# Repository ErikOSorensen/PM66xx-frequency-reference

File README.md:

# PM66xx-frequency-reference

The plan is to build a good 10MHz reference for a PM6674 frequency counter (and those that are related).
This will be a gift to a lucky owner of such a counter.

Inspiration (and physical measurements) are taken from [The sync channel](https://syncchannel.blogspot.com/2016/04/flukephilips-pm66xx-frequency-counter.html),
but I am not so sure about using the internal voltage reference of the oscillator module. I would rather use an external low tempco 
reference such as the [ADR434BRZ](https://www.analog.com/en/products/adr434.html), which means I also need to add
a voltage regulator for this chip.

Looking at the output of my spare CTS 970 oscillator, I think it would also be nice to provide 
a filter on the output, and I've added a 10.5 MHz low pass filter on the bottom of the board.

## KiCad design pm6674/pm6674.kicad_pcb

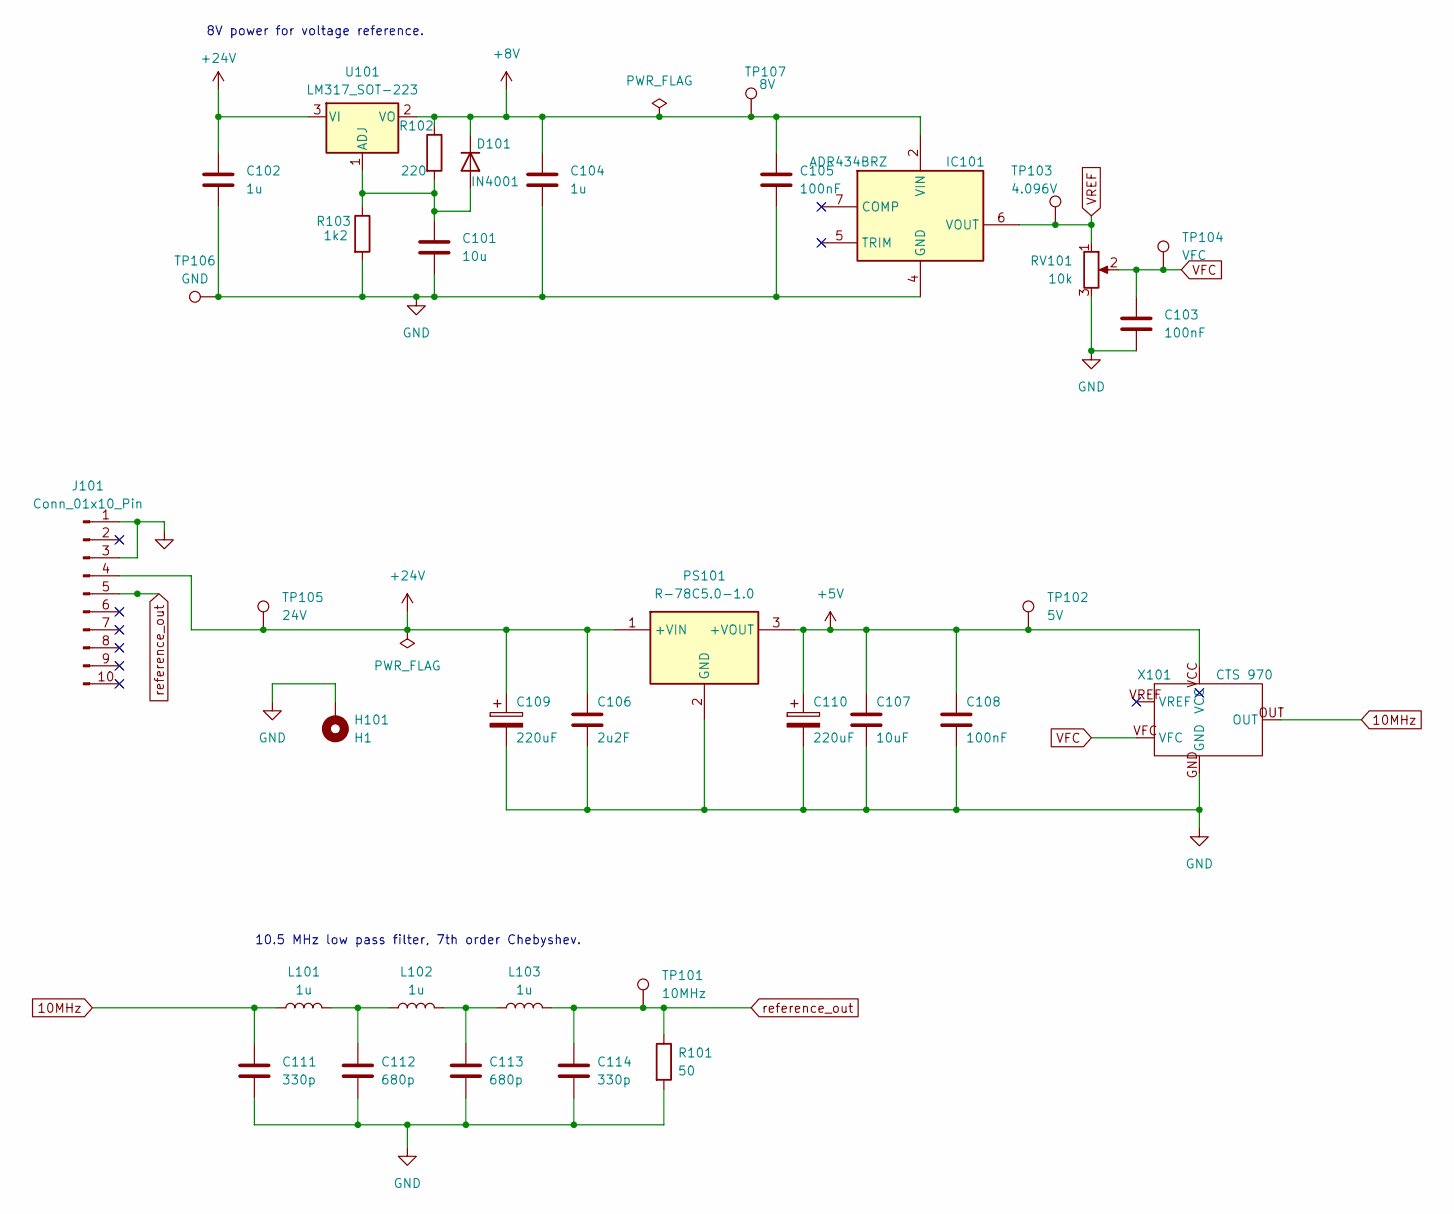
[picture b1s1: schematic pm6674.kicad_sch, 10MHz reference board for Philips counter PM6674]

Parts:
C101: 10u; C_0805_2012Metric
C102, C104: 1u; C_0805_2012Metric
C103, C105, C108: 100nF; C_0805_2012Metric
C106: 2u2F; C_0805_2012Metric
C107: 10uF; C_0805_2012Metric
C109, C110: 220uF; CP_Elec_8x10.5
C111, C114: 330p; C_0805_2012Metric
C112, C113: 680p; C_0805_2012Metric
D101: IN4001; D_SOD-123F
H101: H1; MountingHole_3.2mm_M3_DIN965_Pad_TopBottom
IC101: ADR434BRZ; SOIC127P600X175-8N; Mouser Part Number 584-ADR434BRZ
J101: Conn_01x10_Pin; Molex 22-14-2104
L101, L102, L103: 1u; L_0805_2012Metric
PS101: R-78C5.0-1.0; R78C1210; Mouser Part Number 919-R-78C5.0-1.0
R101: 50; R_0805_2012Metric
R102: 220; R_0805_2012Metric
R103: 1k2; R_0805_2012Metric
RV101: 10k; M64Y503KB40
TP101: 10MHz; PinHeader_1x01_P2.54mm_Vertical
TP102: 5V; PinHeader_1x01_P2.54mm_Vertical
TP103: 4.096V; PinHeader_1x01_P2.54mm_Vertical
TP104: VFC; PinHeader_1x01_P2.54mm_Vertical
TP105: 24V; PinHeader_1x01_P2.54mm_Vertical
TP106: GND; PinHeader_1x01_P2.54mm_Vertical
TP107: 8V; PinHeader_1x01_P2.54mm_Vertical
U101: LM317_SOT-223; SOT-223-3_TabPin2
X101: CTS 970; CTS1960017

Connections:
10MHz: C111.1, L101.1, X101.OUT
+5V: C107.1, C108.1, C110.1, PS101.3 (+VOUT), TP102.1, X101.VCC
+8V: C104.1, C105.1, D101.1 (K), IC101.2 (VIN), R102.1, TP107.1, U101.2 (VO)
+24V: C102.1, C106.1, C109.1, J101.4, PS101.1 (+VIN), TP105.1, U101.3 (VI)
GND: C101.2, C102.2, C103.2, C104.2, C105.2, C106.2, C107.2, C108.2, C109.2, C110.2, C111.2, C112.2, C113.2, C114.2, H101.1, IC101.4 (GND), J101.1, J101.3, PS101.2 (GND), R101.2, R103.2, RV101.3, TP106.1, X101.GND
unnamed: C112.1, L101.2, L102.1
unnamed: C113.1, L102.2, L103.1
unnamed: C101.1, D101.2 (A), R102.2, R103.1, U101.1 (ADJ)
VFC: C103.1, RV101.2, TP104.1, X101.VFC
VREF: IC101.6 (VOUT), RV101.1, TP103.1
reference_out: C114.1, J101.5, L103.2, R101.1, TP101.1

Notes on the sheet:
10.5 MHz low pass filter, 7th order Chebyshev.
8V power for voltage reference.

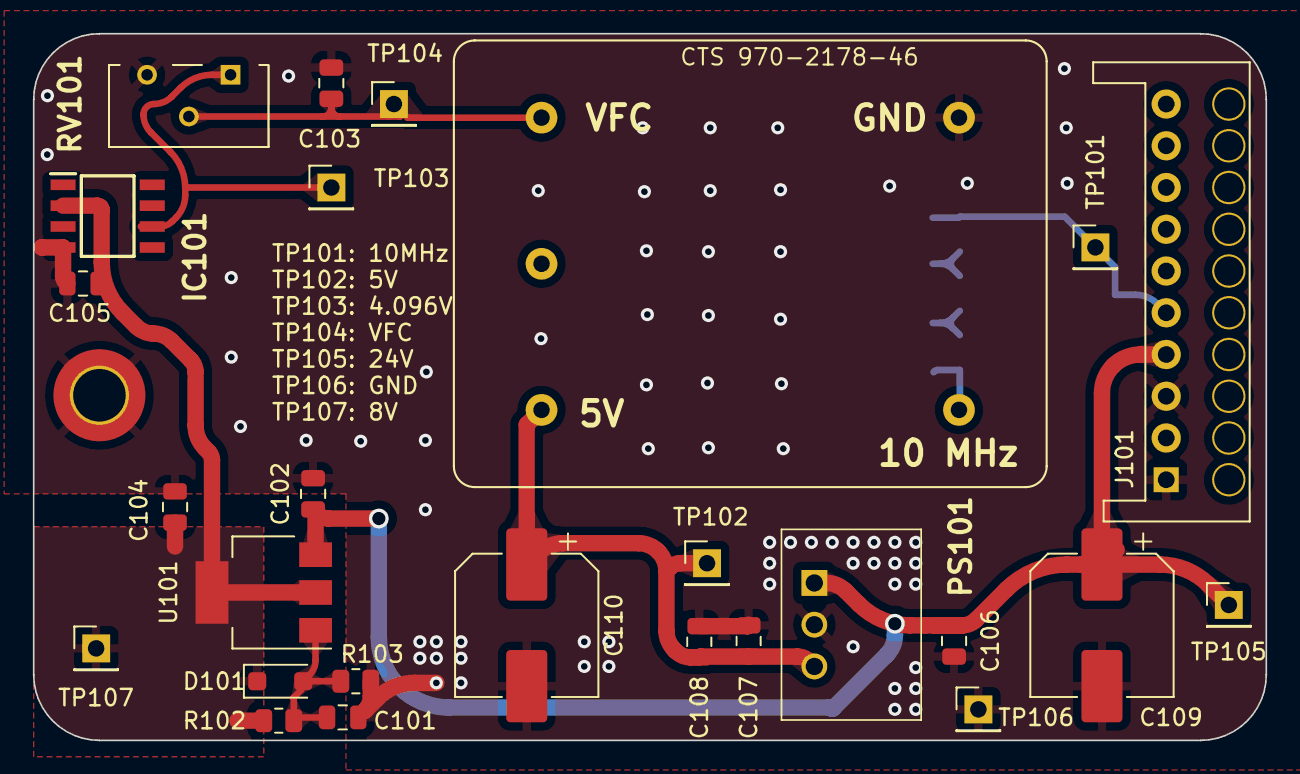
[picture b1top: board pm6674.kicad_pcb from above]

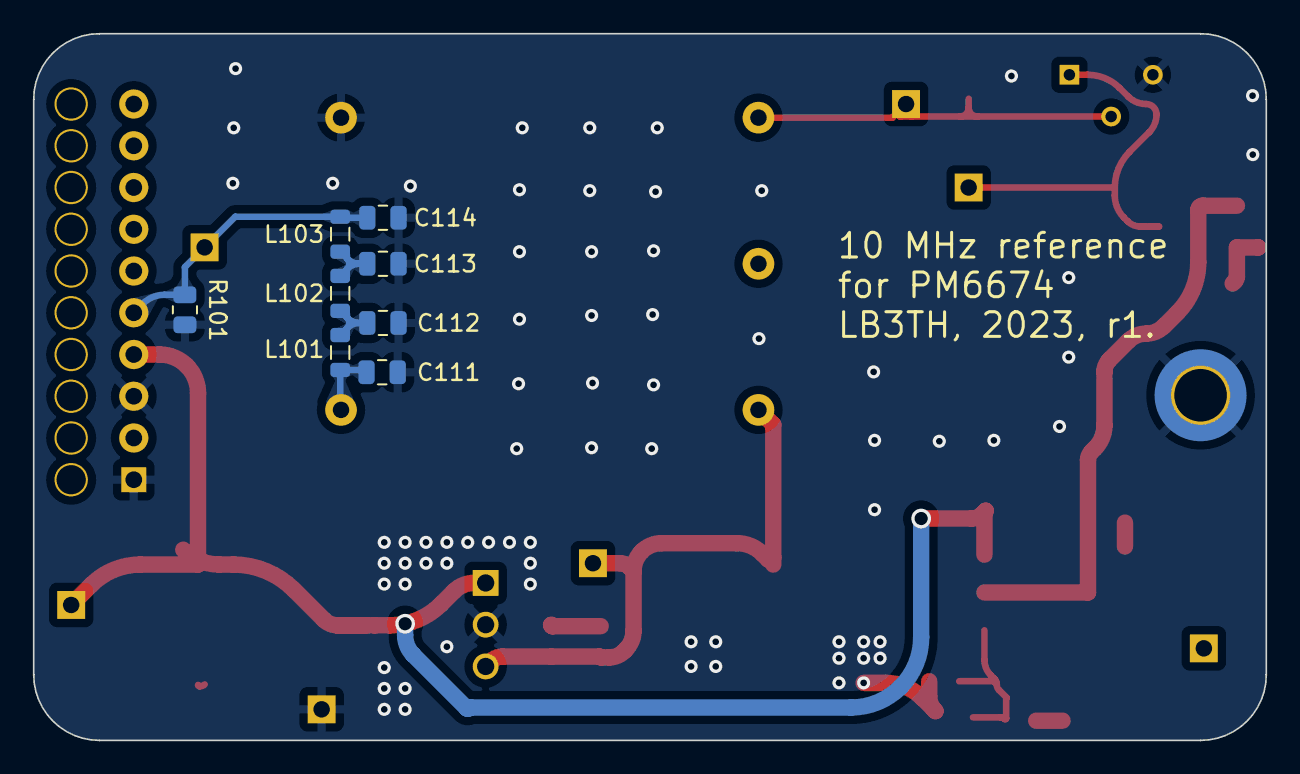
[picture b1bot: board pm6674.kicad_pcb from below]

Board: 2 copper layers, 75.0 x 43.0 mm, 35 parts (8 on the bottom side), 11 nets.

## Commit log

2023-12-07 First cut at board (sent to JLCPCB),
2023-12-20 Final schematics of built-up and tested board.
2023-12-20 Built board and measured the oscillator.
2023-12-20 A bit more description.
2023-12-20 Comment on amplitude.
2023-12-20 Minor update.
2023-12-20 Typos and formatting.
2023-12-22 Added github reference in schematic.
